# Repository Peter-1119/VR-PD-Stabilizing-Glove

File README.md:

# VR-PD-Stabilizing-Glove

# Hand Tremor Stabilization Glove

This project consists of three main components, each responsible for different aspects of the glove device, including microcontroller functionality, hardware design, and computer application development.

## Device Overview

Here is an image of the hand tremor stabilization glove:

The glove is designed to counteract tremors using an embedded motor and sensors to analyze and stabilize hand movements.

## Project Structure

```
📦 HandTremorGlove (Hand Tremor Stabilization Glove Project)
├── 📂 Firmware_STM32 (STM32 Firmware Development)
│   └── Glove (Glove Firmware Code)
├── 📂 Hardware_Design (Hardware Design)
│   ├── KiCad (Circuit Design)
│   ├── TinkerCad (Enclosure Design)
│   └── SolidWorks (Mechanical Design)
└── 📂 Software_Unity (Unity Software Development)
    └──  AirWrite (Virtual Reality Application)
```

## 1. Firmware_STM32
This module manages the embedded system logic and sensor processing using the STM32WB5MMGH6TR microcontroller. Key features and responsibilities include:
* Reading and processing inertial sensor data (accelerometer, gyroscope)
* Implementing tremor detection algorithms and control logic to drive the stabilization motor
* Estimating hand orientation using a custom implementation of the Mahony filter for sensor fusion and posture tracking
* Managing communication protocols such as I2C, UART, and USB, and supporting wireless communication via Bluetooth Low Energy (BLE)
* Optimizing real-time performance and memory usage for embedded deployment

## 2. Hardware_Design
This module focuses on the electronic and mechanical design of the glove, including:
* Circuit design and PCB layout
* 3D modeling and mechanical development
* Power management and port configurations

## 3. Software_Unity
This module develops a VR application for rendering the glove device and tracking hand posture, including:
* Hand gesture tracking and posture detection
* 3D model rendering and interaction
* VR integration and application development

Here is a demonstration of how the glove is visualized and functions in a virtual reality environment:

The VR application allows users to see their hand movements in real-time, providing valuable feedback and interaction within a virtual space.

## Installation & Usage
For detailed installation and development instructions, please refer to the `README.md` files in each subdirectory.

## Contribution
If you are interested in contributing to this project, please submit a Pull Request or contact us.

## License
This project is licensed under the MIT License. See the [LICENSE](LICENSE) file for details.

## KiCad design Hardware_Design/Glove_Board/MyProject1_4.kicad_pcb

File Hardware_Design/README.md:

# Parkinson's Disease Hand Tremor Analysis and Stabilization Device - Hardware Circuit

## Project Description

This project details the hardware circuit design for a wearable device aimed at analyzing and stabilizing hand tremors in Parkinson's disease patients. It encompasses the main control board, a wearable enclosure, and associated circuitry.

## Key Features

*   **Main Control Board Design**:
    *   Selection of a suitable microcontroller (e.g., STM32) as the core processor.
    *   Integration of an inertial measurement unit (IMU) for hand tremor data acquisition.
    *   Integration of a gyroscope to provide physical stabilization.
    *   Design of a power management circuit to ensure stable system operation.
    *   Design of a communication interface (e.g., Bluetooth) for data transmission.
*   **Enclosure Design**:
    *   Design of an ergonomic wearable glove enclosure.
    *   Ensuring secure mounting and protection of hardware components.
    *   Consideration of patient comfort and convenience.
*   **Circuit Design**:
    *   Design of sensor signal processing circuits.
    *   Design of gyroscope control circuits.
    *   Design of power supply and distribution circuits.
    *   Design of communication interface circuits.

## Directory Structure

```
/hardware_Design
├── KiCad/                  # KiCad design files
│   ├── Glove_Board/        # Glove Board Schematics and PCB Layout Files
│   └── InertialSensor/     # IMU Board Schematics and PCB Layout Files
├── SolidWork/              # SolidWorks Design Files
│   └── flywheel/           # Flywheel 3D Model (STL File)
└── TinkerCad/              # Enclosure Models for Glove Board and IMU Board
```

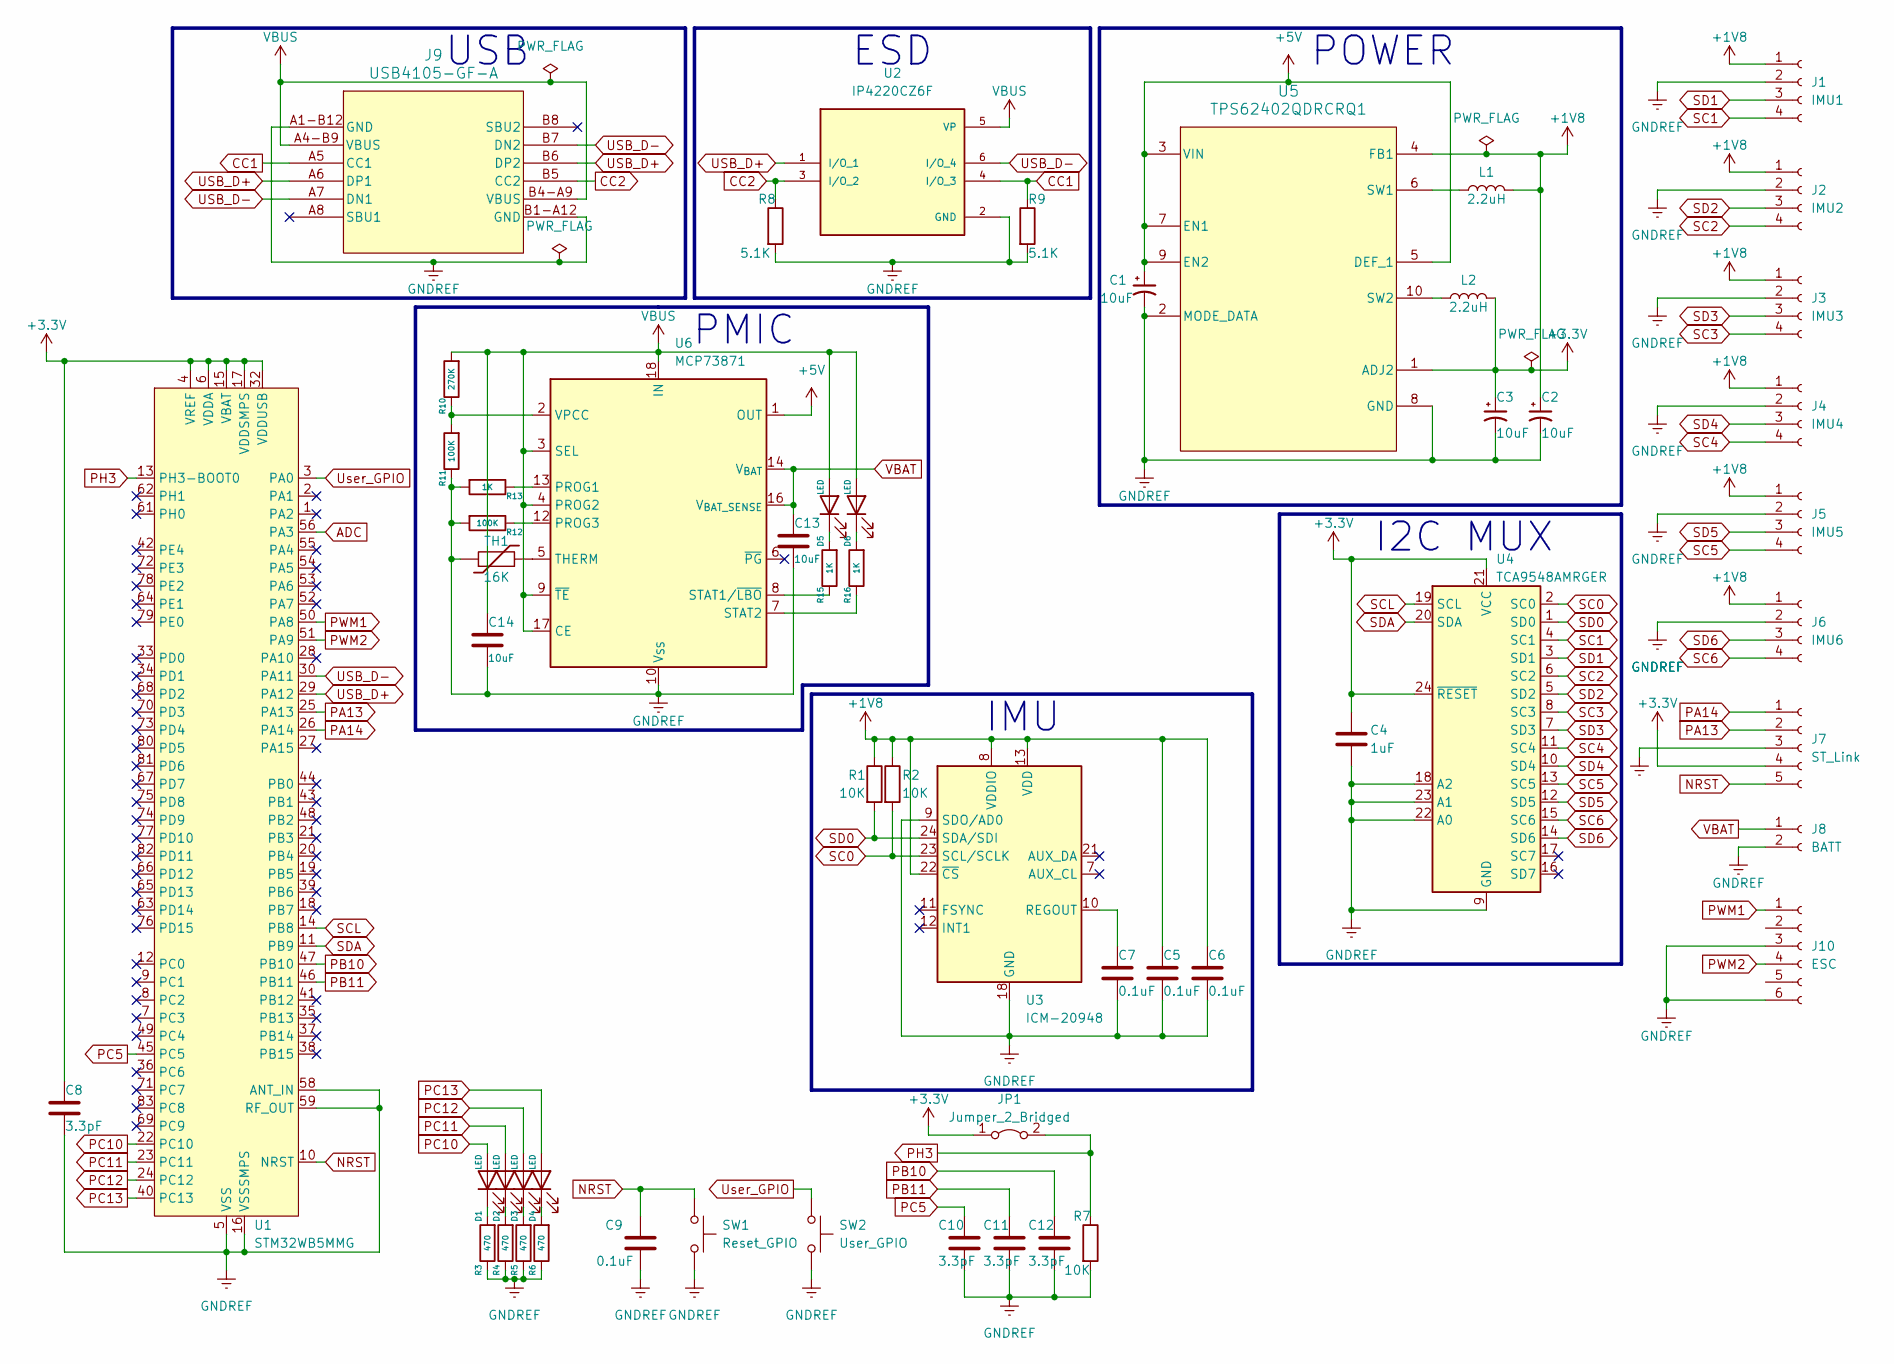
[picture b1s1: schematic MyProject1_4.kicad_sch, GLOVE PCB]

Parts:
C1, C2, C3, C13, C14: 10uF; C_0603_1608Metric
C4: 1uF; C_0603_1608Metric
C5, C6, C7, C9: 0.1uF; C_0603_1608Metric
C8: 3.3pF; C_0603_1608Metric
C10, C11, C12: 3.3pF; C_0402_1005Metric
D1, D2, D3, D4, D5, D6: LED; LED_0603_1608Metric
J1: IMU1; JST_SH_SM04B-SRSS-TB_1x04-1MP_P1.00mm_Horizontal
J2: IMU2; JST_SH_SM04B-SRSS-TB_1x04-1MP_P1.00mm_Horizontal
J3: IMU3; JST_SH_SM04B-SRSS-TB_1x04-1MP_P1.00mm_Horizontal
J4: IMU4; JST_SH_SM04B-SRSS-TB_1x04-1MP_P1.00mm_Horizontal
J5: IMU5; JST_SH_SM04B-SRSS-TB_1x04-1MP_P1.00mm_Horizontal
J6: IMU6; JST_SH_SM04B-SRSS-TB_1x04-1MP_P1.00mm_Horizontal
J7: ST_Link; JST_SH_BM05B-SRSS-TB_1x05-1MP_P1.00mm_Vertical
J8: BATT; JST_SH_SM02B-SRSS-TB_1x02-1MP_P1.00mm_Horizontal
J9: USB4105-GF-A
J10: ESC; PinHeader_1x06_P2.54mm_Horizontal
JP1: Jumper_2_Bridged; PinHeader_1x02_P2.54mm_Vertical
L1, L2: 2.2uH; L_0603_1608Metric
R1, R2, R7: 10K; R_0603_1608Metric
R3, R4, R5, R6: 470; R_0603_1608Metric
R8, R9: 5.1K; R_0603_1608Metric
R10: 270K; R_0603_1608Metric
R11, R12: 100K; R_0603_1608Metric
R13, R15, R16: 1K; R_0603_1608Metric
SW1: Reset_GPIO; SW_SPST_SKQG_WithStem
SW2: User_GPIO; SW_SPST_SKQG_WithStem
TH1: 16K; R_0603_1608Metric
U1: STM32WB5MMG; ST-SiP-LGA-86-11x7.3mm
U2: IP4220CZ6F; PARTREV 5
U3: ICM-20948; InvenSense_QFN-24_3x3mm_P0.4mm
U4: TCA9548AMRGER; Texas_RGE0024C_EP2.1x2.1mm
U5: TPS62402QDRCRQ1
U6: MCP73871; QFN-20-1EP_4x4mm_P0.5mm_EP2.5x2.5mm

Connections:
+1V8: C2.1, C5.1, C6.1, J1.1, J2.1, J3.1, J4.1, J5.1, J6.1, L1.2, R1.1, R2.1, U3.8 (VDDIO), U3.13 (VDD), U3.22 (~CS), U5.4 (FB1)
+3.3V: C3.1, C4.1, C8.1, J7.4, JP1.1 (A), L2.2, U1.4 (VREF), U1.6 (VDDA), U1.15 (VBAT), U1.17 (VDDSMPS), U1.32 (VDDUSB), U4.21 (VCC), U4.24 (~RESET), U5.1 (ADJ2)
+5V: C1.1, U5.3 (VIN), U5.5 (DEF_1), U5.7 (EN1), U5.9 (EN2), U6.1 (OUT), U6.20 (OUT)
ADC: U1.56 (PA3)
CC1: J9.A5 (CC1), R9.1, U2.4 (I/O_3)
CC2: J9.B5 (CC2), R8.1, U2.3 (I/O_2)
GNDREF: C1.2, C2.2, C3.2, C4.2, C5.2, C6.2, C7.2, C8.2, C9.2, C10.2, C11.2, C12.2, C13.2, C14.2, J1.2, J2.2, J3.2, J4.2, J5.2, J6.2, J7.3, J8.2, J9.A1-B12 (GND), J9.B1-A12 (GND), J9.SH1 (GND), J9.SH2 (GND), J9.SH3 (GND), J9.SH4 (GND), J10.3, J10.6, R3.1, R4.1, R5.1, R6.1, R7.2, R8.2, R9.2, R11.1, R12.2, R13.2, SW1.2, SW2.2, TH1.1, U1.5 (VSS), U1.16 (VSSSMPS), U1.31 (VSS), U1.57 (VSS), U1.58 (ANT_IN), U1.59 (RF_OUT), U1.60 (VSS), U1.84 (VSS), U1.86 (VSS), U2.2 (GND), U3.9 (SDO/AD0), U3.18 (GND), U3.20 (GND), U4.9 (GND), U4.18 (A2), U4.22 (A0), U4.23 (A1), U5.2 (MODE_DATA), U5.8 (GND), U5.11, U5.PAD (GND), U6.10 (V_{SS}), U6.11 (V_{SS}), U6.21 (V_{SS})
NRST: C9.1, J7.5, SW1.1, U1.10 (NRST)
unnamed: D1.1 (K), R3.2
unnamed: D2.1 (K), R4.2
unnamed: D3.1 (K), R5.2
unnamed: D4.1 (K), R6.2
unnamed: D5.1 (K), R15.2
unnamed: D6.1 (K), R16.2
unnamed: C7.1, U3.10 (REGOUT)
unnamed: L1.1, U5.6 (SW1)
unnamed: L2.1, U5.10 (SW2)
unnamed: R13.1, U6.13 (PROG1)
unnamed: R12.1, U6.12 (PROG3)
unnamed: R15.1, U6.8 (STAT1/~LBO)
unnamed: R16.1, U6.7 (STAT2)
unnamed: TH1.2, U6.5 (THERM)
unnamed: R10.1, R11.2, U6.2 (VPCC)
PA13: J7.2, U1.25 (PA13)
PA14: J7.1, U1.26 (PA14)
PB10: C12.1, U1.47 (PB10)
PB11: C11.1, U1.46 (PB11)
PC5: C10.1, U1.45 (PC5)
PC10: D1.2 (A), U1.22 (PC10)
PC11: D2.2 (A), U1.23 (PC11)
PC12: D3.2 (A), U1.24 (PC12)
PC13: D4.2 (A), U1.40 (PC13)
PH3: JP1.2 (B), R7.1, U1.13 (PH3-BOOT0)
PWM1: J10.1, U1.50 (PA8)
PWM2: J10.4, U1.51 (PA9)
SC0: R2.2, U3.23 (SCL/SCLK), U4.2 (SC0)
SC1: J1.4, U4.4 (SC1)
SC2: J2.4, U4.6 (SC2)
SC3: J3.4, U4.8 (SC3)
SC4: J4.4, U4.11 (SC4)
SC5: J5.4, U4.13 (SC5)
SC6: J6.4, U4.15 (SC6)
SCL: U1.14 (PB8), U4.19 (SCL)
SD0: R1.2, U3.24 (SDA/SDI), U4.1 (SD0)
SD1: J1.3, U4.3 (SD1)
SD2: J2.3, U4.5 (SD2)
SD3: J3.3, U4.7 (SD3)
SD4: J4.3, U4.10 (SD4)
SD5: J5.3, U4.12 (SD5)
SD6: J6.3, U4.14 (SD6)
SDA: U1.11 (PB9), U4.20 (SDA)
USB_D+: J9.A6 (DP1), J9.B6 (DP2), U1.29 (PA12), U2.1 (I/O_1)
USB_D-: J9.A7 (DN1), J9.B7 (DN2), U1.30 (PA11), U2.6 (I/O_4)
User_GPIO: SW2.1, U1.3 (PA0)
VBAT: C13.1, J8.1, U6.14 (V_{BAT}), U6.15 (V_{BAT}), U6.16 (V_{BAT_SENSE})
VBUS: C14.1, D5.2 (A), D6.2 (A), J9.A4-B9 (VBUS), J9.B4-A9 (VBUS), R10.2, U2.5 (VP), U6.3 (SEL), U6.4 (PROG2), U6.9 (~TE), U6.17 (CE), U6.18 (IN), U6.19 (IN)

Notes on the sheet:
USB
PMIC
POWER
IMU
ESD
I2C MUX

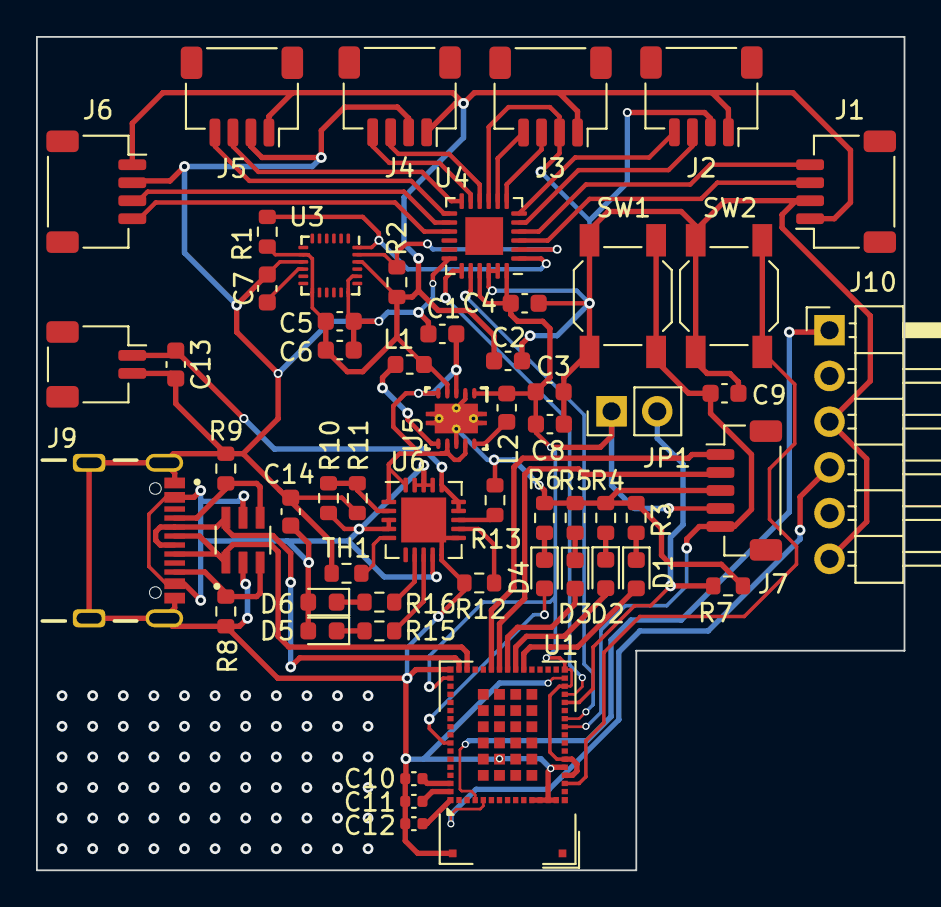
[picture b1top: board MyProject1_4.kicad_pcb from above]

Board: 2 copper layers, 48.2 x 46.3 mm, 57 parts (0 on the bottom side), 55 nets.

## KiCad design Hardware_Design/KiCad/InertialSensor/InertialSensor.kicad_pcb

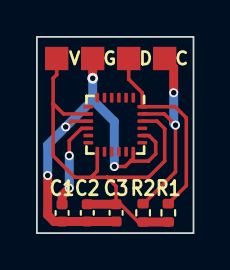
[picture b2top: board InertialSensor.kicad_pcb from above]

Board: 2 copper layers, 8.7 x 10.9 mm, 7 parts (0 on the bottom side), 5 nets.

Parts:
C1, C2, C3: 0.1uF; C_0402_1005Metric
J2: I2C; PAD_01x04
R1, R2: 10K; R_0402_1005Metric
U1: ICM-20948; InvenSense_QFN-24_3x3mm_P0.4mm

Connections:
+1V8: C2.1, C3.1, J2.1, R1.1, R2.1, U1.8 (VDDIO), U1.13 (VDD), U1.22 (~CS)
GNDREF: C1.2, C2.2, C3.2, J2.2, U1.9 (SDO/AD0), U1.18 (GND), U1.20 (GND)
unnamed: C1.1, U1.10 (REGOUT)
SCL: J2.4, R2.2, U1.23 (SCL/SCLK)
SDA: J2.3, R1.2, U1.24 (SDA/SDI)

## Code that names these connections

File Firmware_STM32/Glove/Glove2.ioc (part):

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Mcu.Name=STM32WB5MMGHx
Mcu.Package=LGA86
Mcu.UserName=STM32WB5MMGHx
PA0.GPIOParameters=GPIO_PuPd,GPIO_Label
PA0.GPIO_Label=Btn
PA0.GPIO_PuPd=GPIO_PULLUP
PA0.Signal=GPIO_Input
PA11.Mode=Device
PA11.Signal=USB_DM
PA12.Mode=Device
PA12.Signal=USB_DP
PA13.Mode=Serial_Wire
PA13.Signal=SYS_JTMS-SWDIO
PA14.Mode=Serial_Wire
PA14.Signal=SYS_JTCK-SWCLK
PA8.Signal=S_TIM1_CH1
PA9.Signal=S_TIM1_CH2
PB8.GPIOParameters=GPIO_Speed,GPIO_FM8,GPIO_Pu
PB8.GPIO_FM8=__NULL
PB8.GPIO_Pu=GPIO_PULLUP
PB8.GPIO_Speed=GPIO_SPEED_FREQ_HIGH
PB8.Mode=I2C
PB8.Signal=I2C1_SCL
PB9.GPIOParameters=GPIO_Speed,GPIO_Pu,GPIO_FM9
PB9.GPIO_FM9=__NULL
PB9.GPIO_Pu=GPIO_PULLUP
PB9.GPIO_Speed=GPIO_SPEED_FREQ_HIGH
PB9.Mode=I2C
PB9.Signal=I2C1_SDA
PC10.GPIOParameters=GPIO_Label
PC10.GPIO_Label=LED1
PC10.Signal=GPIO_Output
PC11.GPIOParameters=GPIO_Label
PC11.GPIO_Label=LED2
PC11.Signal=GPIO_Output
PC12.GPIOParameters=GPIO_Label
PC12.GPIO_Label=LED3
PC12.Signal=GPIO_Output
PC13.GPIOParameters=GPIO_Label
PC13.GPIO_Label=LED4
PC13.Signal=GPIO_Output
RCC.HSE_VALUE=32000000
RCC.SYSCLKFreq_VALUE=64000000
RCC.SYSCLKSource=RCC_SYSCLKSOURCE_PLLCLK
board=custom

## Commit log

2025-04-01 Master's thesis works
2025-04-01 Update README.md
    Updated README.md with detailed project structure and descriptions
2025-04-01 Arange Airwrite data files to global_Gesture_Record
2025-04-02 Added device photos and VR demonstration video
2025-04-02 Update README.md
    Updated README.md to include device photos and VR demo
2025-04-02 Added detailed README.md files for hardware, firware, and software components
2025-04-02 Update README.md
    Update README.md gif url
2025-04-02 Update README.md
    Change README.md three main folder name
2025-04-02 Update README.md
    Update Firmware README.md content
2025-04-02 Update README.md
    Update Software README.md Content
2025-04-12 Update README.md
    Update Firmware_STM32 section in README to include STM32WB5MMGH6TR and Mahony filter algorithm
